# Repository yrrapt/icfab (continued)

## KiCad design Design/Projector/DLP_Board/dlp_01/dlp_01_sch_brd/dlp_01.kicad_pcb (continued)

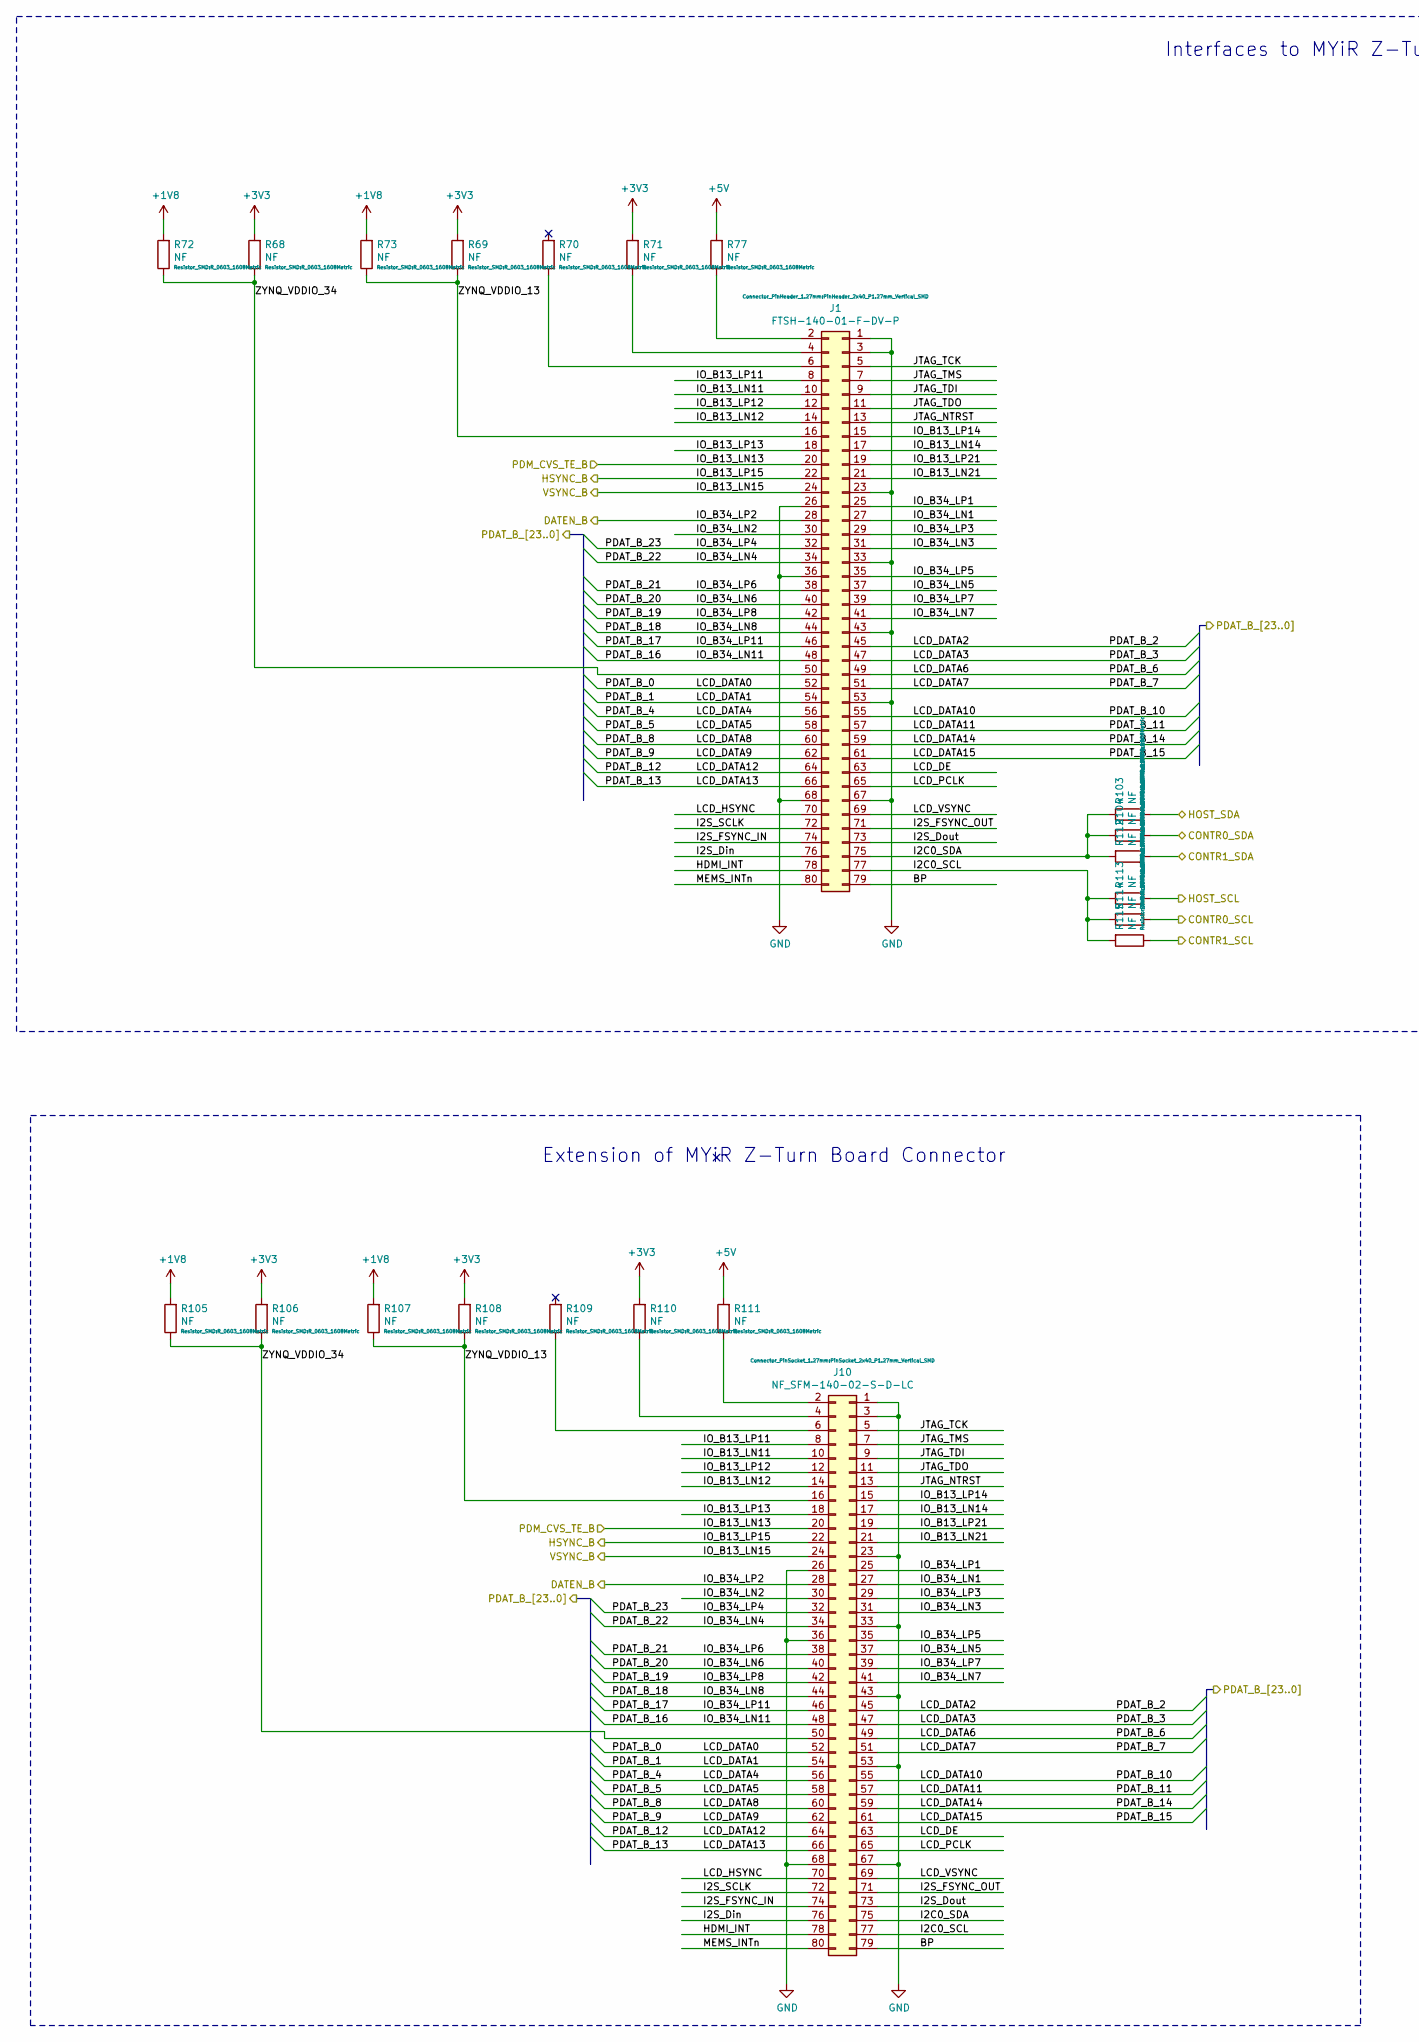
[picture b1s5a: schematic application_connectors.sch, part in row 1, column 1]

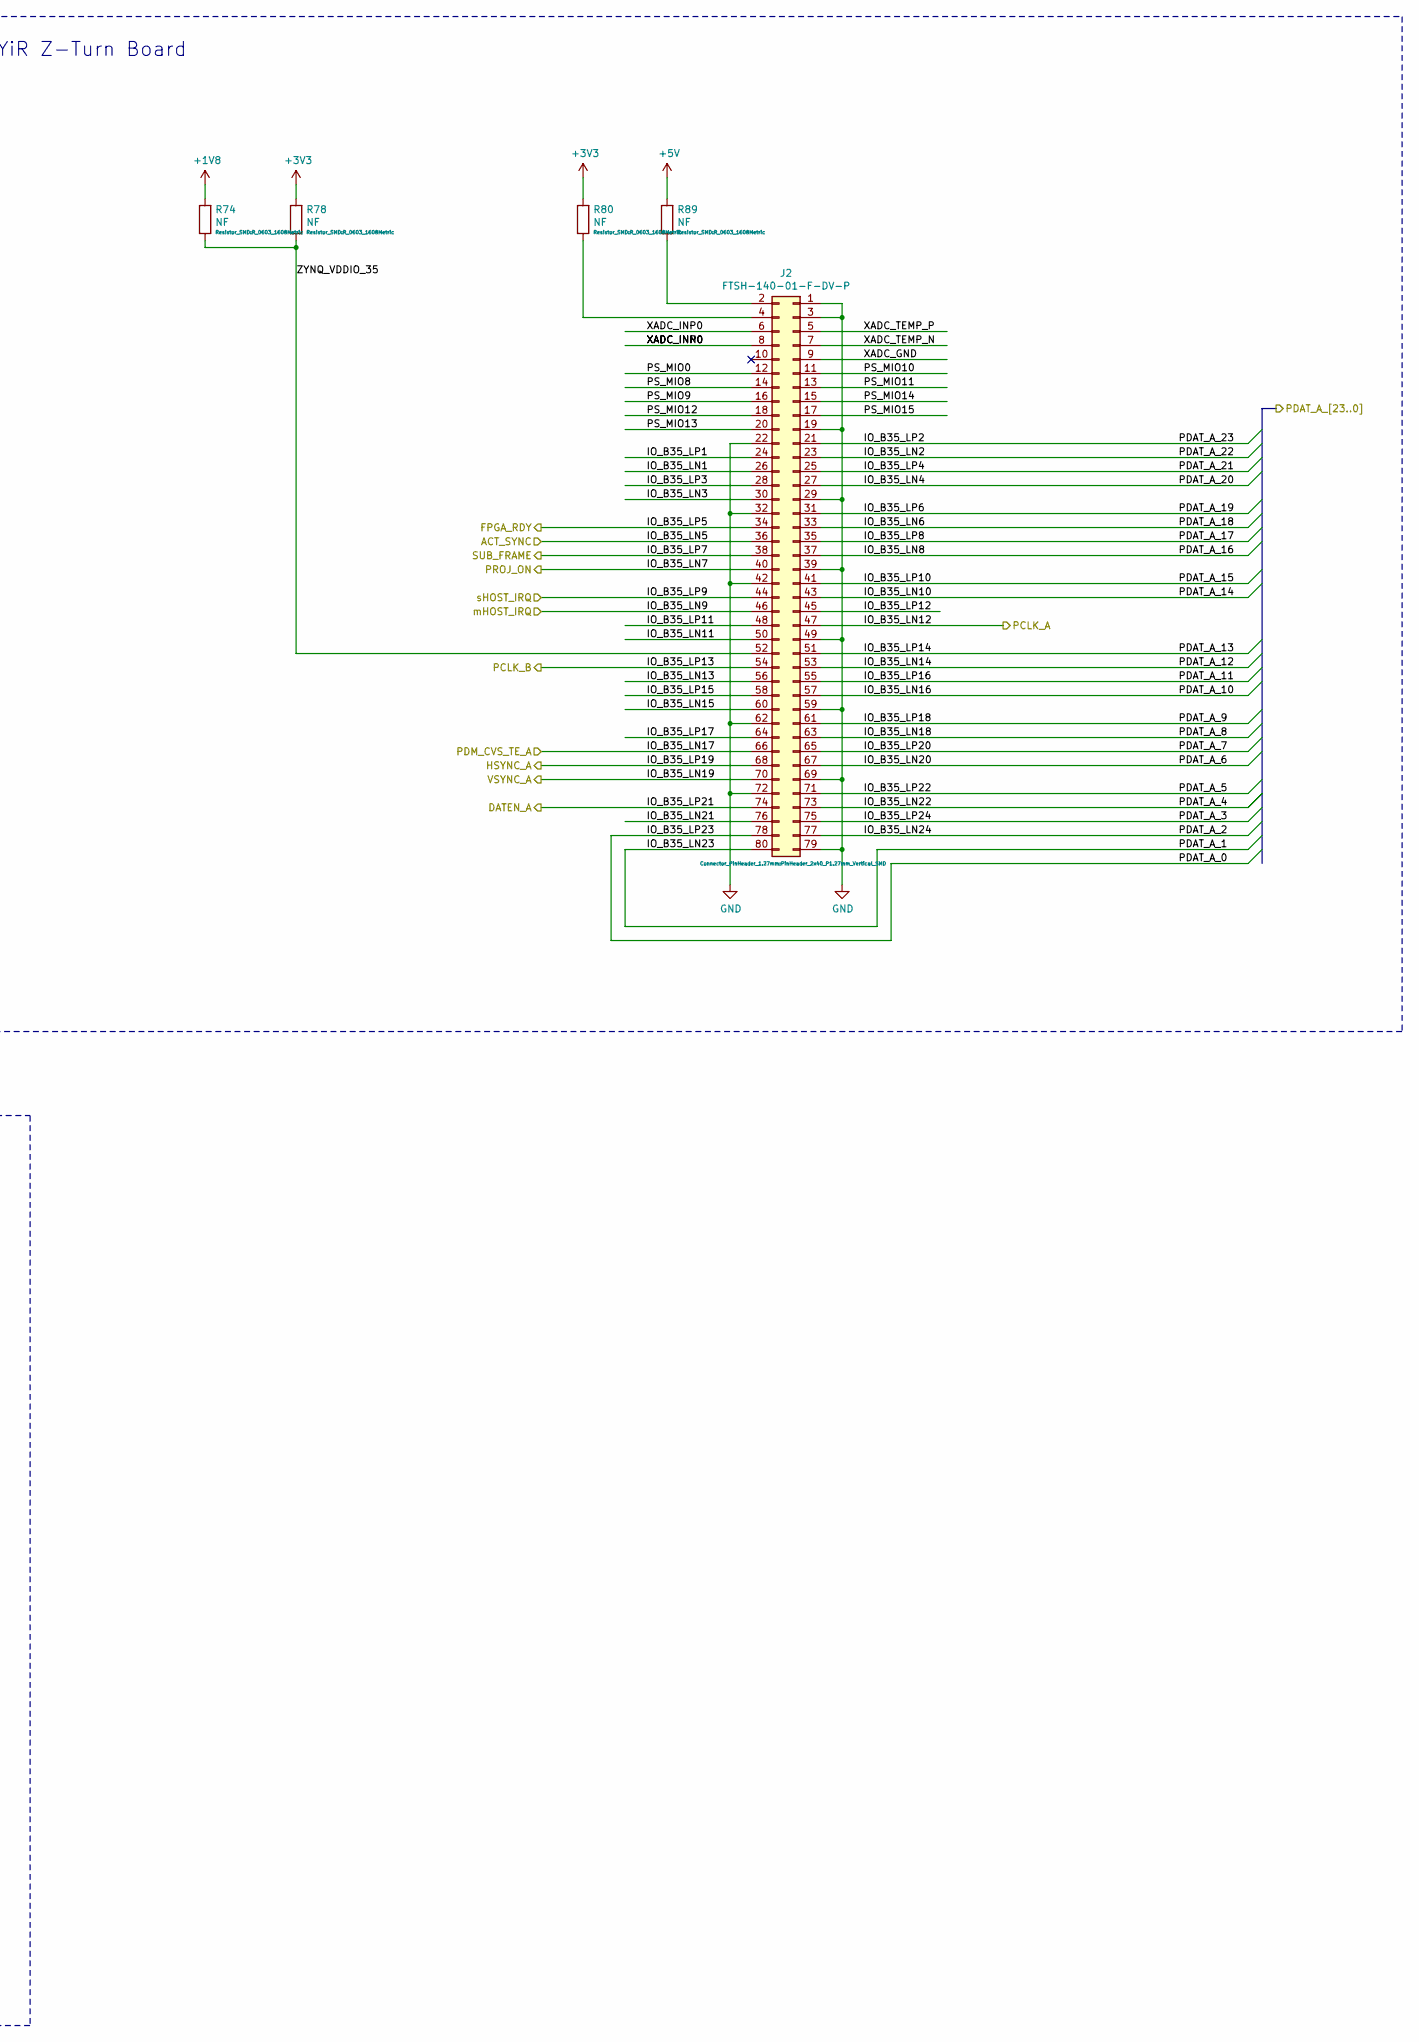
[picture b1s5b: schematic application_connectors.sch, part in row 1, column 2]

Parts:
J1, J2: FTSH-140-01-F-DV-P; PinHeader_2x40_P1.27mm_Vertical_SMD; part-num FTSH-140-01-F-DV-P
J10: NF_SFM-140-02-S-D-LC; PinSocket_2x40_P1.27mm_Vertical_SMD; part-num NF
R68, R69, R70, R71, R72, R73, R74, R77, R78, R80, R89, R103, R104, R105, R106, R107, R108, R109, R110, R111, R112, R113, R114, R115: NF; R_0603_1608Metric; part-num NF

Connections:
+1V8: R72.2, R73.2, R74.2, R105.2, R107.2; also elsewhere on the board
+5V: R77.2, R89.2, R111.2; also elsewhere on the board
/application_connectors/ACT_SYNC: J2.36; also elsewhere on the board
/application_connectors/BP: J1.79, J10.79
/application_connectors/CONTR0_SCL: R114.1; also elsewhere on the board
/application_connectors/CONTR0_SDA: R104.1; also elsewhere on the board
/application_connectors/CONTR1_SCL: R115.1; also elsewhere on the board
/application_connectors/CONTR1_SDA: R112.1; also elsewhere on the board
/application_connectors/DATEN_A: J2.74; also elsewhere on the board
/application_connectors/DATEN_B: J1.28, J10.28; also elsewhere on the board
/application_connectors/FPGA_RDY: J2.34; also elsewhere on the board
/application_connectors/HDMI_INT: J1.78, J10.78
/application_connectors/HOST_SCL: R113.1; also elsewhere on the board
/application_connectors/HOST_SDA: R103.1; also elsewhere on the board
/application_connectors/HSYNC_A: J2.68; also elsewhere on the board
/application_connectors/HSYNC_B: J1.22, J10.22; also elsewhere on the board
/application_connectors/I2C0_SCL: J1.77, J10.77, R113.2, R114.2, R115.2
/application_connectors/I2C0_SDA: J1.75, J10.75, R103.2, R104.2, R112.2
/application_connectors/I2S_Din: J1.76, J10.76
/application_connectors/I2S_Dout: J1.73, J10.73
/application_connectors/I2S_FSYNC_IN: J1.74, J10.74
/application_connectors/I2S_FSYNC_OUT: J1.71, J10.71
/application_connectors/I2S_SCLK: J1.72, J10.72
/application_connectors/IO_B13_LN11: J1.10, J10.10
/application_connectors/IO_B13_LN12: J1.14, J10.14
/application_connectors/IO_B13_LN14: J1.17, J10.17
/application_connectors/IO_B13_LN21: J1.21, J10.21
/application_connectors/IO_B13_LP11: J1.8, J10.8
/application_connectors/IO_B13_LP12: J1.12, J10.12
/application_connectors/IO_B13_LP13: J1.18, J10.18
/application_connectors/IO_B13_LP14: J1.15, J10.15
/application_connectors/IO_B13_LP21: J1.19, J10.19
/application_connectors/IO_B34_LN1: J1.27, J10.27
/application_connectors/IO_B34_LN2: J1.30, J10.30
/application_connectors/IO_B34_LN3: J1.31, J10.31
/application_connectors/IO_B34_LN4: J1.34, J10.34; also elsewhere on the board
/application_connectors/IO_B34_LN5: J1.37, J10.37
/application_connectors/IO_B34_LN6: J1.40, J10.40; also elsewhere on the board
/application_connectors/IO_B34_LN7: J1.41, J10.41
/application_connectors/IO_B34_LN8: J1.44, J10.44; also elsewhere on the board
/application_connectors/IO_B34_LN11: J1.48, J10.48; also elsewhere on the board
/application_connectors/IO_B34_LP1: J1.25, J10.25
/application_connectors/IO_B34_LP3: J1.29, J10.29
/application_connectors/IO_B34_LP4: J1.32, J10.32; also elsewhere on the board
/application_connectors/IO_B34_LP5: J1.35, J10.35
/application_connectors/IO_B34_LP6: J1.38, J10.38; also elsewhere on the board
/application_connectors/IO_B34_LP7: J1.39, J10.39
/application_connectors/IO_B34_LP8: J1.42, J10.42; also elsewhere on the board
/application_connectors/IO_B34_LP11: J1.46, J10.46; also elsewhere on the board
/application_connectors/IO_B35_LN1: J2.26
/application_connectors/IO_B35_LN2: J2.23; also elsewhere on the board
/application_connectors/IO_B35_LN3: J2.30
/application_connectors/IO_B35_LN4: J2.27; also elsewhere on the board
/application_connectors/IO_B35_LN6: J2.33; also elsewhere on the board
/application_connectors/IO_B35_LN8: J2.37; also elsewhere on the board
/application_connectors/IO_B35_LN10: J2.43; also elsewhere on the board
/application_connectors/IO_B35_LN11: J2.50
/application_connectors/IO_B35_LN13: J2.56
/application_connectors/IO_B35_LN14: J2.53; also elsewhere on the board
/application_connectors/IO_B35_LN15: J2.60
/application_connectors/IO_B35_LN16: J2.57; also elsewhere on the board
/application_connectors/IO_B35_LN18: J2.63; also elsewhere on the board
/application_connectors/IO_B35_LN20: J2.67; also elsewhere on the board
/application_connectors/IO_B35_LN21: J2.76
/application_connectors/IO_B35_LN22: J2.73; also elsewhere on the board
/application_connectors/IO_B35_LN23: J2.80; also elsewhere on the board
/application_connectors/IO_B35_LN24: J2.77; also elsewhere on the board
/application_connectors/IO_B35_LP1: J2.24
/application_connectors/IO_B35_LP2: J2.21; also elsewhere on the board
/application_connectors/IO_B35_LP3: J2.28
/application_connectors/IO_B35_LP4: J2.25; also elsewhere on the board
/application_connectors/IO_B35_LP6: J2.31; also elsewhere on the board
/application_connectors/IO_B35_LP8: J2.35; also elsewhere on the board
/application_connectors/IO_B35_LP10: J2.41; also elsewhere on the board
/application_connectors/IO_B35_LP11: J2.48
/application_connectors/IO_B35_LP12: J2.45
/application_connectors/IO_B35_LP14: J2.51; also elsewhere on the board
/application_connectors/IO_B35_LP15: J2.58
/application_connectors/IO_B35_LP16: J2.55; also elsewhere on the board
/application_connectors/IO_B35_LP17: J2.64
/application_connectors/IO_B35_LP18: J2.61; also elsewhere on the board
/application_connectors/IO_B35_LP20: J2.65; also elsewhere on the board
/application_connectors/IO_B35_LP22: J2.71; also elsewhere on the board
/application_connectors/IO_B35_LP23: J2.78; also elsewhere on the board
/application_connectors/IO_B35_LP24: J2.75; also elsewhere on the board
/application_connectors/JTAG_NTRST: J1.13, J10.13
/application_connectors/JTAG_TCK: J1.5, J10.5
/application_connectors/JTAG_TDI: J1.9, J10.9
/application_connectors/JTAG_TDO: J1.11, J10.11
/application_connectors/JTAG_TMS: J1.7, J10.7
/application_connectors/LCD_DATA0: J1.52, J10.52; also elsewhere on the board
/application_connectors/LCD_DATA1: J1.54, J10.54; also elsewhere on the board
/application_connectors/LCD_DATA2: J1.45, J10.45; also elsewhere on the board
/application_connectors/LCD_DATA3: J1.47, J10.47; also elsewhere on the board
/application_connectors/LCD_DATA4: J1.56, J10.56; also elsewhere on the board
/application_connectors/LCD_DATA5: J1.58, J10.58; also elsewhere on the board
/application_connectors/LCD_DATA6: J1.49, J10.49; also elsewhere on the board
/application_connectors/LCD_DATA7: J1.51, J10.51; also elsewhere on the board
/application_connectors/LCD_DATA8: J1.60, J10.60; also elsewhere on the board
/application_connectors/LCD_DATA9: J1.62, J10.62; also elsewhere on the board
/application_connectors/LCD_DATA10: J1.55, J10.55; also elsewhere on the board
/application_connectors/LCD_DATA11: J1.57, J10.57; also elsewhere on the board
/application_connectors/LCD_DATA12: J1.64, J10.64; also elsewhere on the board
/application_connectors/LCD_DATA13: J1.66, J10.66; also elsewhere on the board
/application_connectors/LCD_DATA14: J1.59, J10.59; also elsewhere on the board
/application_connectors/LCD_DATA15: J1.61, J10.61; also elsewhere on the board
/application_connectors/LCD_DE: J1.63, J10.63
/application_connectors/LCD_HSYNC: J1.70, J10.70
/application_connectors/LCD_PCLK: J1.65, J10.65
/application_connectors/LCD_VSYNC: J1.69, J10.69
/application_connectors/MEMS_INTn: J1.80, J10.80
/application_connectors/PCLK_A: J2.47; also elsewhere on the board
/application_connectors/PCLK_B: J2.54; also elsewhere on the board
/application_connectors/PDM_CVS_TE_A: J2.66; also elsewhere on the board
/application_connectors/PDM_CVS_TE_B: J1.20, J10.20; also elsewhere on the board
/application_connectors/PROJ_ON: J2.40; also elsewhere on the board
/application_connectors/PS_MIO0: J2.12
/application_connectors/PS_MIO8: J2.14
/application_connectors/PS_MIO9: J2.16
/application_connectors/PS_MIO10: J2.11
/application_connectors/PS_MIO11: J2.13
/application_connectors/PS_MIO12: J2.18
/application_connectors/PS_MIO13: J2.20
/application_connectors/PS_MIO14: J2.15
/application_connectors/PS_MIO15: J2.17
/application_connectors/SUB_FRAME: J2.38; also elsewhere on the board
/application_connectors/VSYNC_A: J2.70; also elsewhere on the board
/application_connectors/VSYNC_B: J1.24, J10.24; also elsewhere on the board
/application_connectors/XADC_GND: J2.9
/application_connectors/XADC_INN0: J2.6, J2.8
/application_connectors/XADC_TEMP_N: J2.7
/application_connectors/XADC_TEMP_P: J2.5
/application_connectors/ZYNQ_VDDIO_13: J1.16, J10.16, R69.1, R73.1, R107.1, R108.1
/application_connectors/ZYNQ_VDDIO_34: J1.50, J10.50, R68.1, R72.1, R105.1, R106.1
/application_connectors/ZYNQ_VDDIO_35: J2.52, R74.1, R78.1
/application_connectors/mHOST_IRQ: J2.46; also elsewhere on the board
/application_connectors/sHOST_IRQ: J2.44; also elsewhere on the board
GND: J1.1, J1.3, J1.23, J1.26, J1.33, J1.36, J1.43, J1.53, J1.67, J1.68, J2.1, J2.3, J2.19, J2.22, J2.29, J2.32, J2.39, J2.42, J2.49, J2.59, J2.62, J2.69, J2.72, J2.79, J10.1, J10.3, J10.23, J10.26, J10.33, J10.36, J10.43, J10.53, J10.67, J10.68; also elsewhere on the board
unnamed: J1.2, R77.1
unnamed: J1.4, R71.1
unnamed: J1.6, R70.1
unnamed: J2.2, R89.1
unnamed: J2.4, R80.1
unnamed: J10.2, R111.1
unnamed: J10.4, R110.1
unnamed: J10.6, R109.1

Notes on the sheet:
Interfaces to MYiR Z-Turn Board
Extension of MYiR Z-Turn Board Connector

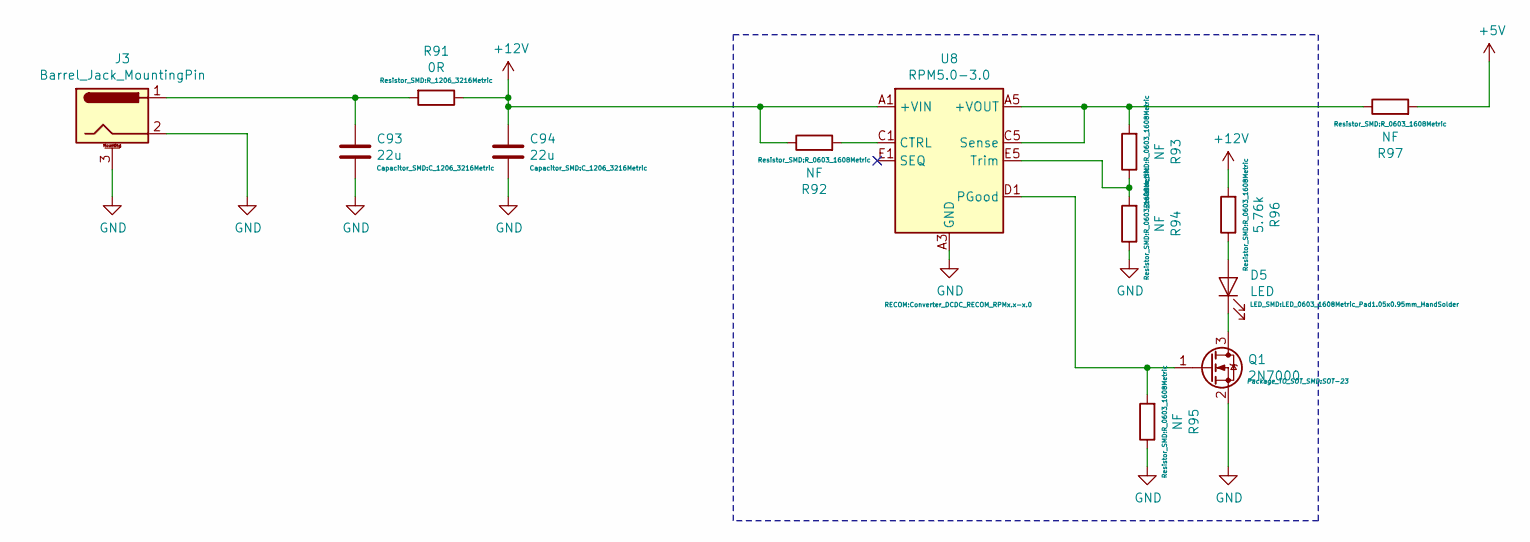
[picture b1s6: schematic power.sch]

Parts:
C93, C94: 22u; C_1206_3216Metric; part-num 12063D226MAT2A
D5: LED; LED_0603_1608Metric_Pad1.05x0.95mm_HandSolder; part-num 150060AS75000
J3: Barrel_Jack_MountingPin; BarrelJack_Horizontal; part-num KLDHCX-0202-AC-1
Q1: 2N7000; SOT-23; part-num 2N7000
R91: 0R; R_1206_3216Metric; part-num CRCW12060000Z0EAC
R92, R93, R94, R95, R97: NF; R_0603_1608Metric; part-num NF
R96: 5.76k; R_0603_1608Metric; part-num CRCW06035K76FKEA
U8: RPM5.0-3.0; Converter_DCDC_RECOM_RPMx.x-x.0; part-num RPM5.0-3.0

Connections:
+5V: R97.2; also elsewhere on the board
+12V: C94.1, R91.1, R92.1, R96.2, U8.A1 (+VIN), U8.A2 (+VIN); also elsewhere on the board
GND: C93.2, C94.2, J3.2, J3.3 (MountPin), Q1.2 (S), R94.1, R95.1, U8.A3 (GND), U8.A4 (GND), U8.B1 (GND), U8.B2 (GND), U8.B3 (GND), U8.B4 (GND), U8.C2 (GND), U8.C3 (GND), U8.C4 (GND), U8.D2 (GND), U8.D3 (GND), U8.D4 (GND), U8.D5 (GND), U8.E3 (GND), U8.E4 (GND); also elsewhere on the board
unnamed: C93.1, J3.1, R91.2
unnamed: D5.1 (K), Q1.3 (D)
unnamed: D5.2 (A), R96.1
unnamed: Q1.1 (G), R95.2, U8.D1 (PGood)
unnamed: R92.2, U8.C1 (CTRL)
unnamed: R93.1, R94.2, U8.E5 (Trim)
unnamed: R93.2, R97.1, U8.A5 (+VOUT), U8.B5 (+VOUT), U8.C5 (Sense)
